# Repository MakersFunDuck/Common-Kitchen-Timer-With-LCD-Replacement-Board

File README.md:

# Common Kitchen Timer With an LCD-Replacement Board
A replacement PCB board for common 4 digit 7 segment LCD kitchen timers

It uses a cheap TM1621D LCD driver. You can solder either Attiny13A, or ESP12E module. 

The "Print" function can print out supported letters on the screen. However it is not optimised for memory constains for Attiny13A.

**Folder descriptions:**

**Datasheets:** Where datasheets of the components are located (also translations from Chinese)

**Fabrication files:** Gerber files. You can just upload those to any PCB manufacturer website to get your PCB.

**Firmware:** Code examples which is written using Arduino framework.

**KiCAD files:** KiCAD schematics and PCB files

**Schematics and Layout files:** PDF files for the PCB and Schematics.

If you want to use another LCD, or make your own PCB designs, I explained them in a video if you are interested. 
https://youtu.be/JNZbfLtlbZA

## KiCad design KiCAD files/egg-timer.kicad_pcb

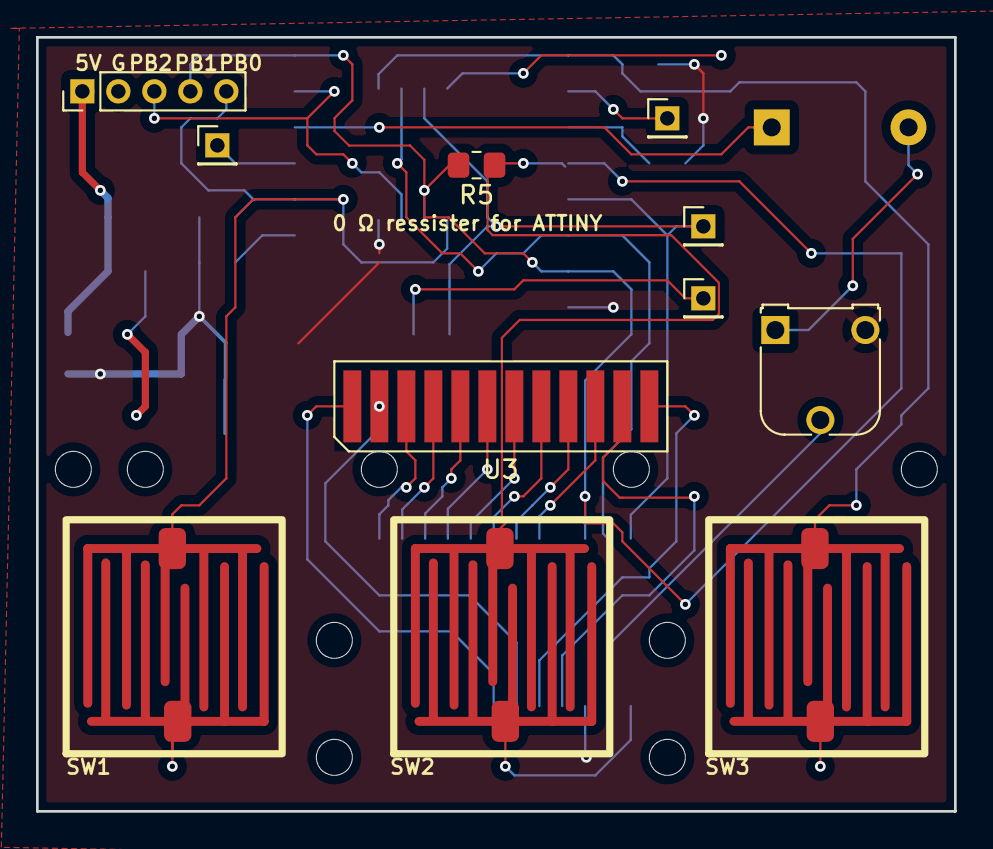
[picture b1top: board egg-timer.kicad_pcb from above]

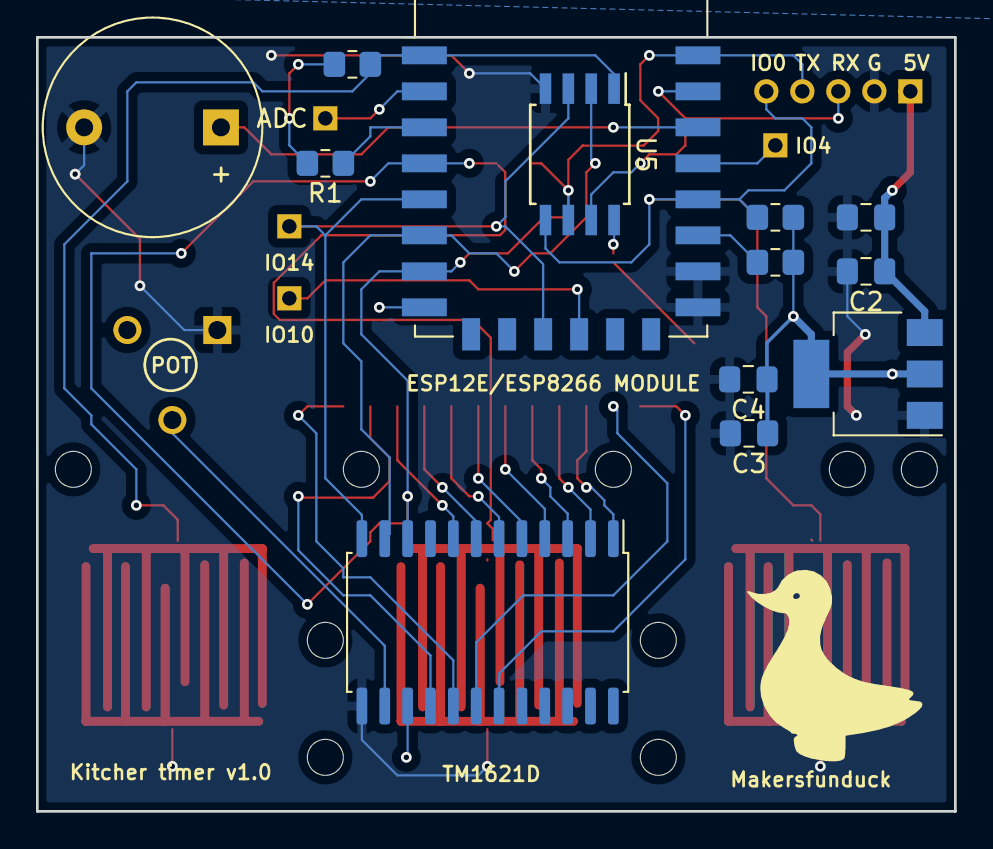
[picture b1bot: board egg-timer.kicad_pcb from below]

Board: 2 copper layers, 51.0 x 43.0 mm, 24 parts (13 on the bottom side), 29 nets.

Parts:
BZ1: Buzzer; Buzzer_12x9.5RM7.6
C1, C3: 10uF; C_0805_2012Metric_Pad1.18x1.45mm_HandSolder
C2, C4: 100nF; C_0805_2012Metric_Pad1.18x1.45mm_HandSolder
J1: Conn_01x05; PinHeader_1x05_P2.00mm_Vertical
J2, J3, J4, J5: Conn_01x01; PinHeader_1x01_P2.00mm_Vertical
R1, R2, R4: 1k; R_0805_2012Metric_Pad1.20x1.40mm_HandSolder
R3: 1K; R_0805_2012Metric_Pad1.20x1.40mm_HandSolder
R5: 0Ω; R_0805_2012Metric_Pad1.20x1.40mm_HandSolder
RV1: R_Potentiometer; Potentiometer_Runtron_RM-065_Vertical
SW1, SW2, SW3: SW_Push; contact pad
U1: ESP-12E
U2: TM1621D; SOIC-24W_7.5x15.4mm_P1.27mm
U3: bare-lcd; bare-lcd-footprint12
U4: AMS1117-3.3; SOT-223-3_TabPin2
U5: ATtiny13A-S; SOIC-8W_5.3x5.3mm_P1.27mm

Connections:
5V: C1.1, C2.1, J1.1, U4.3 (VI)
+3.3V: C3.1, C4.1, R1.2, R2.1, R3.1, R4.1, RV1.3, U1.8 (VCC), U2.15 (VDD), U4.2 (VO), U5.8 (VCC)
ADC: J5.1, U1.2 (ADC)
COM0: U2.16 (COM0), U3.11
COM1: U2.17 (COM1), U3.12
COM2: U2.18 (COM2), U3.2
COM3: U2.19 (COM3), U3.1
GND: BZ1.2 (+), C1.2, C2.2, C3.2, C4.2, J1.2, RV1.1, SW1.1, SW2.1, SW3.1, U1.15 (GND), U1.16 (GPIO15), U2.13 (VSS), U4.1 (GND), U5.4 (GND)
IO0: J1.5, R3.2, SW1.2, U1.18 (GPIO0), U5.5 (PB0)
IO4: J4.1, U1.19 (GPIO4)
IO5: BZ1.1 (-), U1.20 (GPIO5)
IO10: J3.1, U1.12 (GPIO10)
IO12: U1.6 (GPIO12), U2.11 (WR#), U5.2 (PB3)
IO13: J1.4, R5.2, U1.7 (GPIO13), U1.22 (GPIO1/TXD), U2.10 (CS#), U5.6 (PB1)
IO14: J2.1, U1.5 (GPIO14), U1.11 (GPIO9), U2.12 (DATA#), U5.3 (PB4)
IO16: R5.1, SW2.2, U1.4 (GPIO16)
unnamed: R1.1, U1.3 (EN)
unnamed: R4.2, U1.17 (GPIO2)
unnamed: RV1.2, U2.14 (VLCD)
PB2: J1.3, U1.21 (GPIO3/RXD), U5.7 (PB2)
RST: R2.2, SW3.2, U1.1 (~RST), U5.1 (~RESET/PB5)
SEG1: U2.1 (SEG17), U3.3
SEG2: U2.2 (SEG16), U3.4
SEG3: U2.3 (SEG15), U3.5
SEG4: U2.4 (SEG14), U3.6
SEG5: U2.5 (SEG13), U3.7
SEG6: U2.6 (SEG12), U3.8
SEG7: U2.7 (SEG11), U3.9
SEG8: U2.8 (SEG10), U3.10

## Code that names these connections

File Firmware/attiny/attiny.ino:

#include "TM1621D.h"

#define PIN_TM1621D_BL     PB0
#define PIN_TM1621D_CS     PB1
#define PIN_TM1621D_RW     PB3
#define PIN_TM1621D_DATA   PB4












struct DisplayConfig {
    uint8_t m4b;   // MSB 4 bits
    uint8_t l4b;   // LSB 4 bits
    bool bitHL;    // High bits or Low bits
};

uint8_t displayMemory[18];  // Display Segments Memory

DisplayConfig digMap[18] = { //High, Low
    {11,10,  true}, { 9, 8,  true}, { 7, 6,  true},  { 5, 4,  true}, { 3, 2,  true}, { 1, 0,  true}, // Row 1
    {11,10, false}, { 9, 8, false}, { 7, 6, false},  { 5, 4, false}, { 3, 2, false}, { 1, 0, false}, // Row 2
    {12,13,  true}, {14,15,  true}, {16,17,  true},  {12,13, false}, {14,15, false}, {16,17, false}  // Row 3
};

uint8_t segments[] = {
    //GBDCFAME
    0b01111101,  // 0
    0b01010000,  // 1
    0b11100101,  // 2
    0b11110100,  // 3
    0b11011000,  // 4
    0b10111100,  // 5
    0b10111101,  // 6
    0b01010100,  // 7
    0b11111101,  // 8
    0b11111100,  // 9
    0b00000000   // [Empty]
};

TM1621D ht(PIN_TM1621D_CS, PIN_TM1621D_RW, PIN_TM1621D_DATA);

void writeDigit(uint8_t d, uint8_t num){
    DisplayConfig df = digMap[d];
    writeSegments(d, segments[num]);
}

void writeSegments(uint8_t d, uint8_t segData){
    DisplayConfig df = digMap[d];
    uint8_t high4Bit = segData >> 4;
    uint8_t low4Bit  = segData & 0b1111;
    
    if( df.bitHL ){
        high4Bit = high4Bit << 4;
        low4Bit  = low4Bit << 4;
        displayMemory[df.m4b] = displayMemory[df.m4b] & 0b00001111;
        displayMemory[df.l4b] = displayMemory[df.l4b] & 0b00001111;
        displayMemory[df.m4b] = displayMemory[df.m4b] | high4Bit;
        displayMemory[df.l4b] = displayMemory[df.l4b] | low4Bit;
    }else{
        displayMemory[df.m4b] = displayMemory[df.m4b] & 0b11110000;
        displayMemory[df.l4b] = displayMemory[df.l4b] & 0b11110000;
        displayMemory[df.m4b] = displayMemory[df.m4b] | high4Bit;
        displayMemory[df.l4b] = displayMemory[df.l4b] | low4Bit;
    }
    
    ht.write(df.m4b, displayMemory[df.m4b]);
    ht.write(df.l4b, displayMemory[df.l4b]);
}


void setup() {
  
    uint8_t i;
    pinMode(PIN_TM1621D_BL, OUTPUT);
    digitalWrite(PIN_TM1621D_BL, LOW);

    ht.begin();
    
    ht.sendCommand(TM1621D::RC256K);
    ht.sendCommand(TM1621D::BIAS_THIRD_4_COM);
    ht.sendCommand(TM1621D::SYS_EN);
    ht.sendCommand(TM1621D::LCD_ON);

    //Clear display
    for(i=0; i<18; i++){
        displayMemory[i] = 0;
        ht.write(i,0);
    }
  

    digitalWrite(PIN_TM1621D_BL, HIGH); //Turn on backlight LED
    

    digitalWrite(PIN_TM1621D_BL, LOW); //Turn off backlight LED
    
    // write all segments (even dp)
    for(i=0; i<18; i++){
        ht.write(i, 0xFF);
       
        delay( 2000 );
    }

    
    //Clear display
    for(i=0; i<18; i++){
        displayMemory[i] = 0;
        ht.write(i,0);
    }
}

void loop() {

      for(int i=5; i<9; i++){
      /* 
      ht.write(i, 0b00000001); //e
        delay( 1000 );
        ht.write(i, 0b00000010); //ms
        delay( 1000 );

        ht.write(i, 0b00000100); //a
        delay( 1000 );
        ht.write(i, 0b00001000); //f
        delay( 1000 );
        ht.write(i, 0b00010000); //c
        delay( 1000 );

        ht.write(i, 0b00100000); //d
        delay( 1000 );
        ht.write(i, 0b10000000); // g
        delay( 1000 );
        ht.write(i, 0b01000000); //b
        delay( 1000 );
        */
    for(int J=0; J<10; J++){
       ht.write(i, segments[J]); //b
        delay( 1000 );
        }
    }
}



  

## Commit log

2024-01-17 Sample screen picture
2024-01-20 Create LICENSE
